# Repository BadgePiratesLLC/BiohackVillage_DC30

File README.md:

# BiohackVillage_DC30
DefCon 30 biohack Village Badge

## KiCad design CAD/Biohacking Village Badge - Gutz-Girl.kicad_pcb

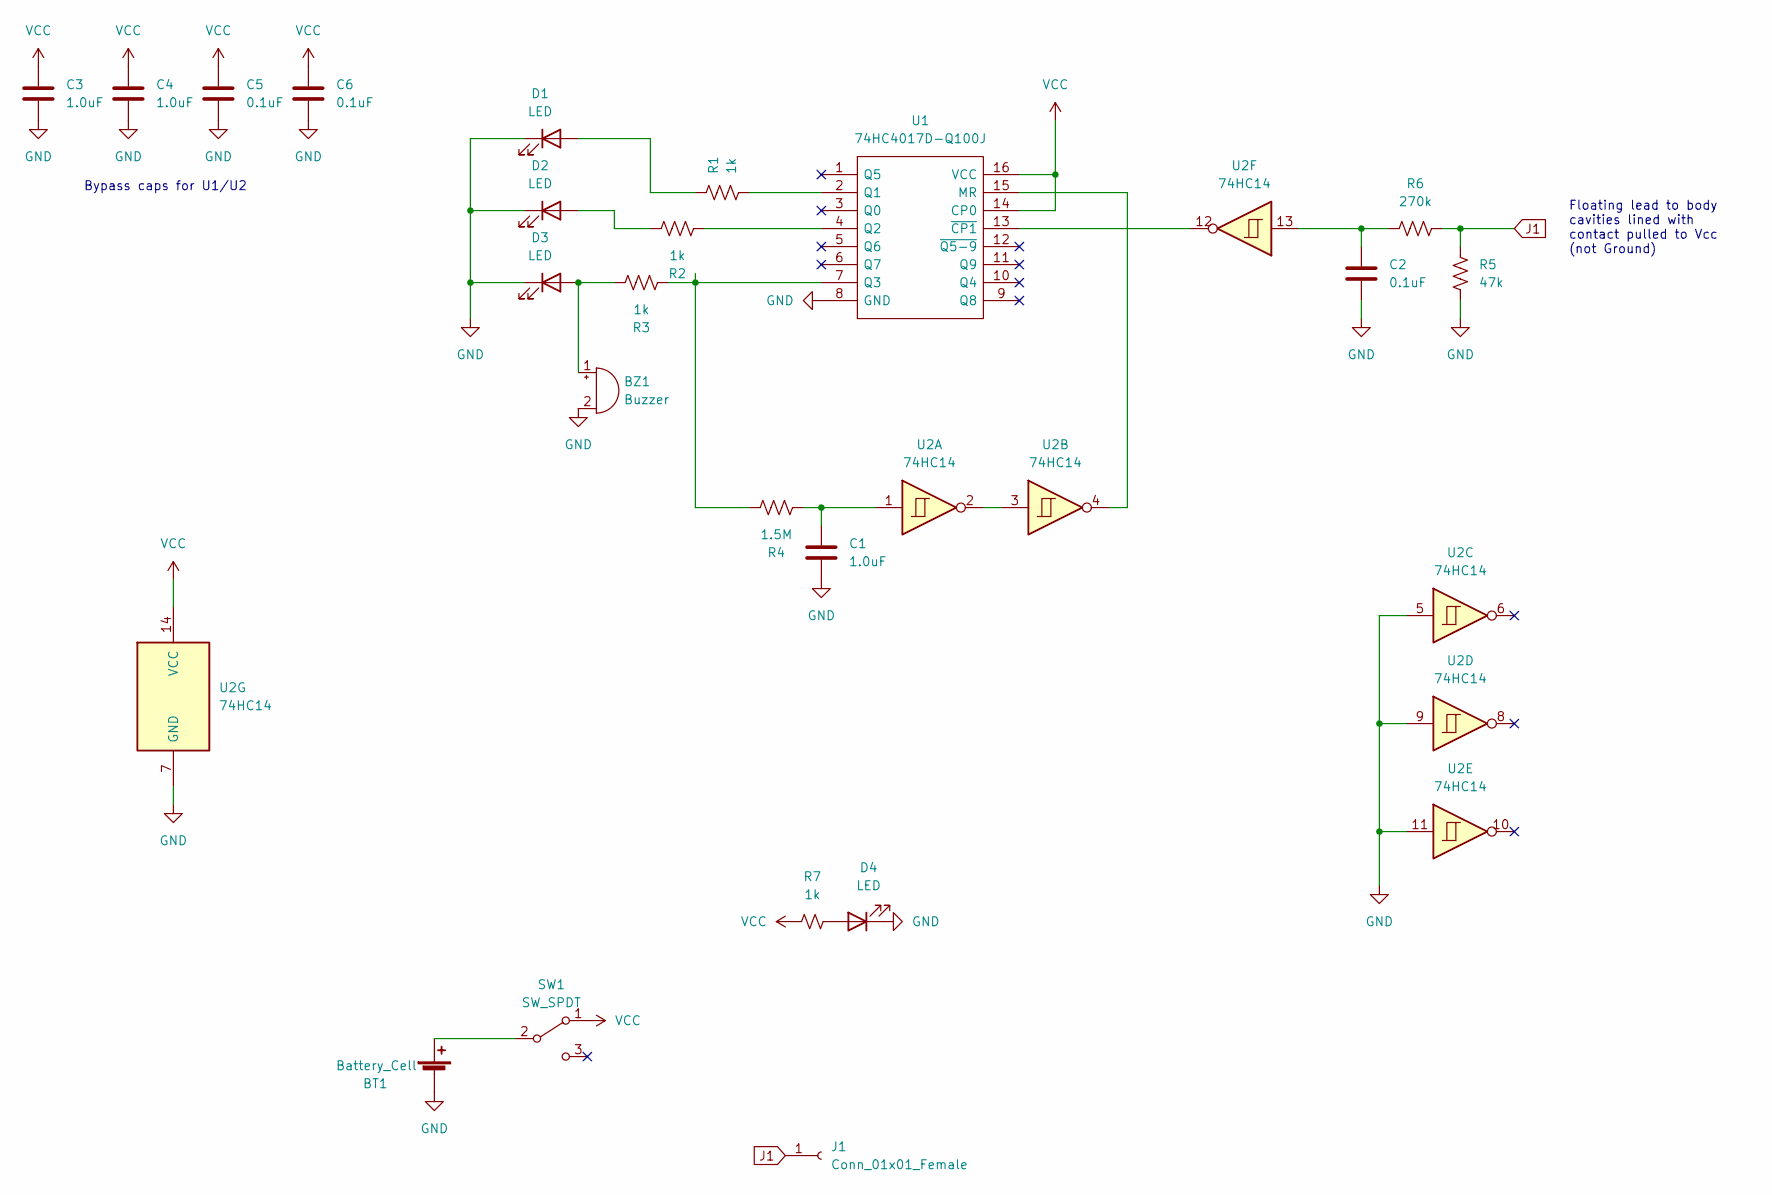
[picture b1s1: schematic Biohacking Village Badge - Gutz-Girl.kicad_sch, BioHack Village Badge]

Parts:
BT1: Battery_Cell; BATHLD006SMT
BZ1: Buzzer; MagneticBuzzer_CUI_CMT-8504-100-SMT
C1, C3, C4: 1.0uF; C_0805_2012Metric
C2, C5, C6: 0.1uF; C_0805_2012Metric
D1, D2, D3: LED; LED_Osram_Lx_P47F_D2mm_ReverseMount_Proper_Mask Only
D4: LED; LED_1206_3216Metric
J1: Conn_01x01_Female; PinSocket_1x01_P2.54mm_Vertical
R1, R2, R3, R7: 1k; R_1206_3216Metric
R4: 1.5M; R_1206_3216Metric
R5: 47k; R_1206_3216Metric
R6: 270k; R_1206_3216Metric
SW1: SW_SPDT; SW_SPDT_PCM12
U1: 74HC4017D-Q100J; SOIC127P600X175-16N; Mouser Part Number 771-74HC4017D-Q100J
U2: 74HC14; SO-14_3.9x8.65mm_P1.27mm

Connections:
GND: BT1.2 (-), BZ1.2 (+), C1.2, C2.2, C3.2, C4.2, C5.2, C6.2, D1.1 (K), D2.1 (K), D3.1 (K), D4.1 (K), R5.1, U1.8 (GND), U2.5, U2.7 (GND), U2.9, U2.11; also elsewhere on the board
J1: J1.1, R5.2, R6.1
unnamed 2: BT1.1 (+), SW1.2 (B), SW1.3 (C); also elsewhere on the board
unnamed: BZ1.1 (-), D3.2 (A), R3.1
unnamed: C1.1, R4.2, U2.1
unnamed: C2.1, R6.2, U2.13
unnamed: D1.2 (A), R1.1
unnamed: D2.2 (A), R2.1
unnamed: D4.2 (A), R7.2
unnamed: R1.2, U1.2 (Q1)
unnamed: R2.2, U1.4 (Q2)
unnamed: R3.2, R4.1, U1.7 (Q3)
unnamed: U1.13 (~CP1), U2.12
unnamed: U1.15 (MR), U2.4
unnamed: U2.2, U2.3
VCC: C3.1, C4.1, C5.1, C6.1, R7.1, SW1.1 (A), U1.14 (CP0), U1.16 (VCC), U2.14 (VCC)

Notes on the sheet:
Floating lead to body cavities lined with contact pulled to Vcc (not Ground)
Bypass caps for U1/U2

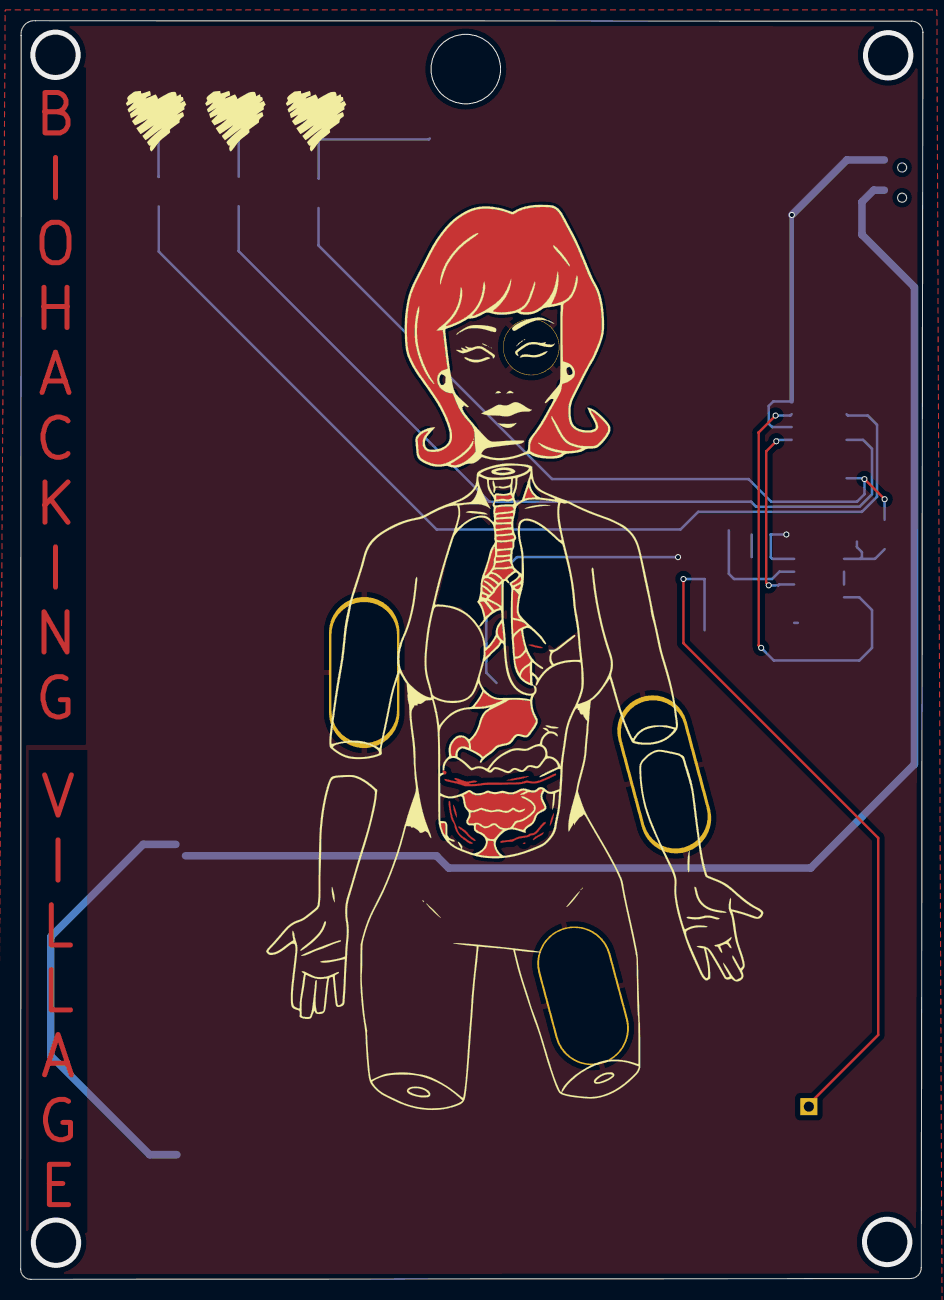
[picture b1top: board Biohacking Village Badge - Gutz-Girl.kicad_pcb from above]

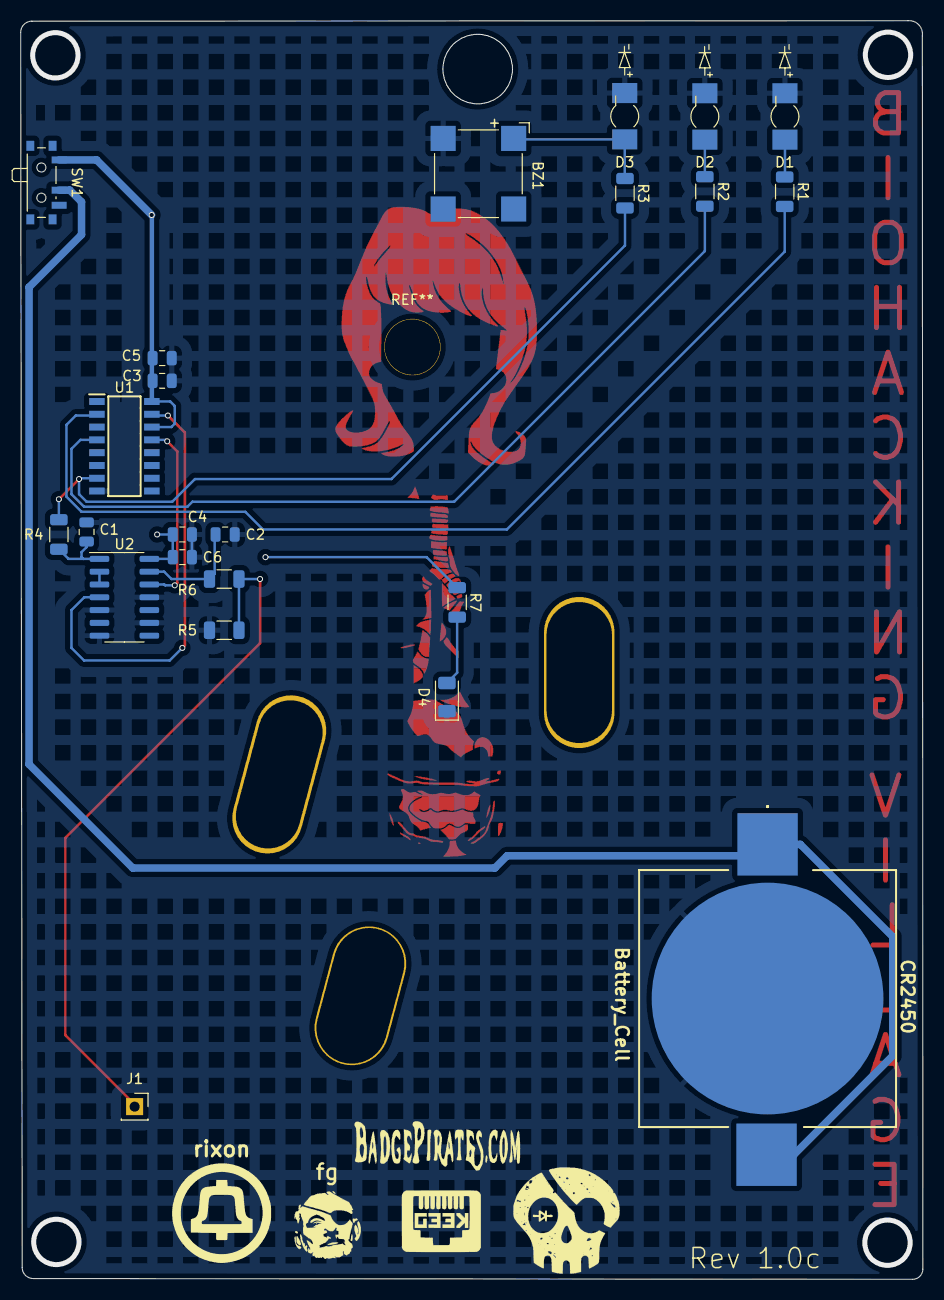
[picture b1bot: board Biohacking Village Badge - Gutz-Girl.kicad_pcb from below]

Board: 2 copper layers, 89.5 x 124.9 mm, 23 parts (20 on the bottom side), 16 nets.

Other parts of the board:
CR2450: Battery_Cell; BATHLD006SMT

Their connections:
GND: CR2450.2 (-); also elsewhere on the board
unnamed 2: CR2450.1 (+); also elsewhere on the board
